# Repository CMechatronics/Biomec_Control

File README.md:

# Control. Biomec UMA

Biomec es una iniciativa de la Universidad de Málaga orientada al desarrollo de soluciones de ingeniería aplicadas a prótesis de mano electrónicas. El proyecto parte del estudio de señales electromiográficas (EMG), obtenidas a partir de la actividad muscular, para convertirlas en información útil de control.

La señal biológica se adquiere mediante un sistema de medida basado en el ADS1198 y se comunica con un microcontrolador encargado de procesarla. A partir de ese tratamiento es posible definir umbrales de activación y generar órdenes de control que permitan accionar los motores de la prótesis de forma coordinada.

El trabajo integra varias disciplinas técnicas, entre ellas mecánica, control, electrónica y diseño de sistemas embebidos.

## Objetivo del repositorio

Este repositorio reúne el trabajo del departamento de control y sirve como base para organizar el avance del proyecto, documentar decisiones técnicas y centralizar tareas, diseños y pruebas de desarrollo.

## Contexto técnico

El planteamiento del sistema se apoya en la adquisición diferencial de bioseñales, el acondicionamiento de la señal y su posterior interpretación para control. En la práctica, esto exige una interfaz fiable entre el cuerpo y la electrónica, así como un tratamiento adecuado del ruido, la amplitud de la señal y la sincronización con el sistema de actuación.

## Alcance

- Estudio y adquisición de señales EMG.
- Interfaz entre el sensor biológico y la electrónica de control.
- Procesamiento de señal para detección de umbrales y eventos.
- Integración con actuadores para el control de la mano protésica.

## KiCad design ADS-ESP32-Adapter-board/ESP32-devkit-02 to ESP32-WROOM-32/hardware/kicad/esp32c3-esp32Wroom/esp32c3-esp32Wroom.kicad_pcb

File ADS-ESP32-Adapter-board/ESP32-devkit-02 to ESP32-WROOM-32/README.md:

# Placa adaptadora: ESP32-DevKit-C3-02 → ESP32-WROOM-32

## Resumen ejecutivo

Este directorio contiene el diseño y documentación de la placa adaptadora que permite migrar del ESP32-C3 DevKitC-02 al ESP32-WROOM-32, manteniendo compatibilidad total con la interfaz del ADS1198 y reduciendo la dependencia de hardware específico.

## Motivación técnica

El ESP32-C3 DevKitC-02 presenta limitaciones de disponibilidad en el mercado y restricciones en número de pines GPIO. El ESP32-WROOM-32 ofrece:
- Mayor capacidad de procesamiento (2 núcleos vs 1)
- Más pines GPIO disponibles (34 vs 13)
- Mayor memoria RAM y flash
- Mejor disponibilidad en el mercado
- Mejor rendimiento energético en aplicaciones con WiFi/Bluetooth

La placa adaptadora permite cambiar de microcontrolador sin modificar la base del sistema ni el firmware de procesamiento de señal.

---

## Especificaciones técnicas comparativas

### Arquitectura y procesamiento

| Aspecto | ESP32-C3 DevKit-02 | ESP32-WROOM-32 |
|--------|-------------------|------------------|
| **Arquitectura** | RISC-V 32-bit | Xtensa 32-bit dual-core |
| **Núcleos** | 1 @ 160 MHz | 2 @ 80/160 MHz (configurable) |
| **Caché** | 16 KB I + 8 KB D | 32 KB I + 32 KB D (per core) |
| **Memoria RAM** | 400 KB | 520 KB |
| **Flash externo** | 4 MB | 4/8/16 MB (configurable) |
| **Voltaje** | 3.3 V | 3.3 V |
| **Consumo activo** | ~40-60 mA | ~80-100 mA (dual-core) |

### Conectividad

| Característica | ESP32-C3 | ESP32-WROOM-32 |
|---|---|---|
| **WiFi** | 802.11 b/g/n (2.4 GHz) | 802.11 b/g/n (2.4 GHz) |
| **Bluetooth** | LE 5.0 only | Classic 5.0 + LE 4.2 |
| **Antena** | Integrada PCB | Integrada PCB |
| **TX Power** | +15 dBm (WiFi), +4 dBm (BLE) | +20 dBm (WiFi), +4 dBm (BLE) |

### Periféricos disponibles

| Periférico | ESP32-C3 | ESP32-WROOM-32 |
|---|---|---|
| **UART** | 2 (GPIO20/21, GPIO5/6 alt) | 3 (GPIO1/3, GPIO9/10, GPIO17/16 alt) |
| **SPI** | 1 maestro (GPIO6/7/2/10) | 3 (SPI2 en GPIO12-15, SPI3 en GPIO17-22) |
| **I²C** | 2 | 2 (GPIO21/22) |
| **GPIO analógicos** | 11 canales ADC | 12 canales ADC (algunos compartidos con SPI) |
| **PWM** | 6 canales | 16 canales |
| **Timer** | 2 | 4 |
| **RTC** | Sí | Sí |

---

## Mapa de equivalencias GPIO

### Interfaz del ADS1198 (SPI principal)

| Función | ESP32-C3 DevKit-02 | ESP32-WROOM-32 | Notas |
|---------|-------------------|-----------------|-------|
| **FE_RESET** | GPIO0 | GPIO32 | Reinicio del front-end ADS1198 |
| **FE_DRDY** | GPIO1 | GPIO35 | Data Ready del ADS1198 |
| **SPI_MISO** | GPIO2 | GPIO12 | ESP32 ← ADS1198 (datos) |
| **FE_START** | GPIO3 | GPIO33 | Inicio de conversión del ADS |
| **SPI_CLK** | GPIO6 | GPIO14 | Reloj SPI |
| **SPI_MOSI** | GPIO7 | GPIO13 | ESP32 → ADS1198 (datos) |
| **FE_CS** | GPIO10 | GPIO15 | Chip Select del ADS1198 |

### Pines de soporte general

| Función | ESP32-C3 | ESP32-WROOM-32 | Observaciones |
|---------|----------|---|---|
| **3V3** | Pin 2 | Pin 2 | Alimentación lógica |
| **5V** | Pin 1 | Pin 1 | Entrada de alimentación externa |
| **GND** | Pins 3, 4, 5 | Pins 3, 4, 5 | Referencia común (múltiples puntos) |
| **USB D+** | GPIO19 | GPIO25 | No usado en este diseño |
| **USB D-** | GPIO18 | GPIO26 | No usado en este diseño |
| **EN/RST** | GPIO9 | GPIO EN | Reinicio del microcontrolador |
| **BOOT** | GPIO8 | GPIO0 alt | Modo de arranque |

### GPIO disponibles adicionales

Pines libres para futuras expansiones o depuración:

**ESP32-WROOM-32:**
- GPIO4, GPIO5, GPIO23, GPIO27, GPIO34, GPIO36, GPIO37, GPIO38, GPIO39
- GPIO25, GPIO26 (para USB si se requiere, no usado actualmente)

---

## Consideraciones de diseño

### Alimentación

- **Voltaje de entrada recomendado:** 5V ± 0.5V
- **Regulador:** LDO de bajo ruido para generar 3.3V
- **Capacitores:** 
  - Entrada: 10 µF (para estabilidad de línea de 5V)
  - Salida: 10 µF + 100 nF (cerca del ESP32-WROOM-32)
- **Consumo pico esperado:** ~150 mA (con WiFi activo)

### Aislamiento de ruido

El ADS1198 es un front-end de bajo ruido sensible a perturbaciones electromagnéticas:

- Separación física entre zona de alimentación del ADS1198 y ESP32-WROOM-32
- Plano de GND continuo bajo el ADS1198
- Vías de paso (via stitching) alrededor del área de señal analógica
- Capacitores de desacoplamiento locales (100 nF) para cada pin de alimentación del ADS

### Interfaces SPI

**ESP32-WROOM-32 SPI2 (usado):**
- Frecuencia configurada: 2 MHz (conservadora para estabilidad)
- Bus compartido con la interfaz SD (cuidado si se agrega soporte SD)
- Modo: SPI Master, CPOL=0, CPHA=0

**Líneas de control especiales:**
- **DRDY** es una línea de interrupción activa baja
- **CS** debe mantenerse baja durante toda la transacción SPI
- **RESET** debe pulsarse al menos 2 µs

### Protección ESD

- Protección ESD serie en líneas de señal analógica (optional, depende de ambiente)
- Protección TVS en líneas de GPIO si están expuestas

---

## Estructura del proyecto

```
ESP32-devkit-02 to ESP32-WROOM-32/
├── docs/
│   ├── planteamiento.pdf          # Análisis y justificación técnica
│   └── README.md                  # Este archivo
├── hardware/
│   └── kicad/
│       ├── esp32c3-esp32Wroom/   # Diseño principal de la placa
│       │   ├── esp32c3-esp32Wroom.kicad_sch
│       │   ├── esp32c3-esp32Wroom.kicad_pcb
│       │   ├── esp32c3-esp32Wroom.kicad_pro
│       │   └── .history/          # Historial de cambios
│       └── MiESP32Lib/            # Librería de símbolos personalizados
│           └── MiESP32Lib.kicad_sym
├── src/                           # Firmware en desarrollo
├── lib/                           # Librerías reutilizables
├── signal_processing/             # Módulos de procesamiento de señal
└── tools/                         # Scripts y utilidades
```

---

## Cambios de firmware necesarios

### Configuración de pines en PlatformIO/Arduino

```cpp
// Configuración SPI
#define SPI_MISO  12
#define SPI_MOSI  13
#define SPI_CLK   14
#define SPI_CS    15

// Señales de control del ADS1198
#define ADS_RESET 32
#define ADS_DRDY  35
#define ADS_START 33

// Verificar que el SPI esté configurado para SPI2:
// hspi_host en lugar de vspi_host
```

### Inicialización del SPI

```cpp
spi_bus_config_t buscfg = {
    .mosi_io_num = SPI_MOSI,
    .miso_io_num = SPI_MISO,
    .sclk_io_num = SPI_CLK,
    .quadwp_io_num = -1,
    .quadhd_io_num = -1,
    .max_transfer_sz = 4094,
};

esp_err_t ret = spi_bus_initialize(HSPI_HOST, &buscfg, DMA_CHAN_AUTO);
```

---

## Validación y pruebas

### Checklist de verificación hardware

- [ ] Continuidad en pistas de alimentación (5V, 3.3V, GND)
- [ ] Ausencia de cortocircuitos entre pistas de señal
- [ ] Voltaje de salida del regulador: 3.3V ± 0.1V
- [ ] Continuidad en líneas SPI (CLK, MOSI, MISO, CS)
- [ ] Continuidad en líneas de control (RESET, DRDY, START)
- [ ] Resistencia de Pull-up en DRDY (si está configurado)

### Pruebas funcionales

1. **Lectura de registro de identity del ADS1198**
   - Leer registro 0x00 (debe retornar ID del chip)
   - Repetir 10 veces para validar comunicación estable

2. **Adquisición de datos**
   - Configurar ADS1198 en modo continuo
   - Leer datos continuamente
   - Verificar rango esperado (±12V entrada → ±32768 digital)

3. **Rendimiento**
   - Medir frecuencia de muestreo efectiva (debe ser ≥ 1000 Hz)
   - Medir latencia de DRDY a lectura completa

4. **WiFi/Bluetooth** (si se requiere)
   - Verificar conectividad WiFi
   - Verificar rango de señal
   - Evaluar impacto en ruido de ADC

---

## Diferencias operacionales clave

### Ventajas del ESP32-WROOM-32

✅ **Dual-core:** Posibilidad de ejecutar procesamiento pesado en core 1 mientras core 0 gestiona SPI  
✅ **Más memoria:** Espacio para algoritmos de filtrado más complejos  
✅ **Mejor rendimiento WiFi:** Core dedicado disponible  
✅ **Mayor disponibilidad:** Componente más común en el mercado  
✅ **Menores costos:** Precio más estable y comprobado  

### Limitaciones a considerar

⚠️ **Consumo superior:** ~50 mA adicionales con dual-core activo  
⚠️ **Mayor tamaño:** PCB del módulo es más grande  
⚠️ **Configuración SPI:** Usa SPI2 en lugar de SPI1  
⚠️ **Pin layout diferente:** Requiere rediseño de placa adaptadora  
⚠️ **ADC compartido:** Algunos pines ADC comparten funciones con SPI (GPIO12, GPIO13, GPIO14, GPIO15)

---

## Hoja de ruta

| Fase | Tarea | Estado | Target |
|------|-------|--------|--------|
| 1 | Diseño esquemático y layout PCB | ✅ Completado | - |
| 2 | Fabricación de prototipo | ⏳ En progreso | 2-3 semanas |
| 3 | Validación eléctrica del prototipo | ⏳ En progreso | - |
| 4 | Adaptación de firmware a pines nuevos | ⏳ En progreso | - |
| 5 | Pruebas funcionales del sistema completo | ⏹️ Pendiente | - |
| 6 | Generación de PCB final | ⏹️ Pendiente | - |
| 7 | Documentación de fabricación | ⏹️ Pendiente | - |

---

## Referencias y recursos

### Datasheets
- [ESP32-C3 Datasheet](https://www.espressif.com/sites/default/files/documentation/esp32-c3_datasheet_en.pdf)
- [ESP32 (WROOM-32) Datasheet](https://www.espressif.com/sites/default/files/documentation/esp32_datasheet_en.pdf)
- [ADS1198 Datasheet](https://www.ti.com/lit/ds/symlink/ads1198.pdf)

### Librerías y soporte
- [ESP-IDF (Espressif IoT Development Framework)](https://github.com/espressif/esp-idf)
- [Arduino-ESP32](https://github.com/espressif/arduino-esp32)
- [KiCad Documentation](https://docs.kicad.org/)

### Herramientas recomendadas
- KiCad 6.0+ para editar esquemáticos y PCB
- PlatformIO o Arduino IDE para programación
- Logic Analyzer de bajo coste para debug SPI

---

## Contacto y soporte

Para consultas técnicas sobre este diseño, consultar la documentación de Biomec UMA o la rama `develop` del repositorio.

**Última actualización:** Agosto 2026  
**Autor:** Departamento de Control, Biomec UMA  
**Licencia:** Ver archivo LICENSE en la raíz del repositorio

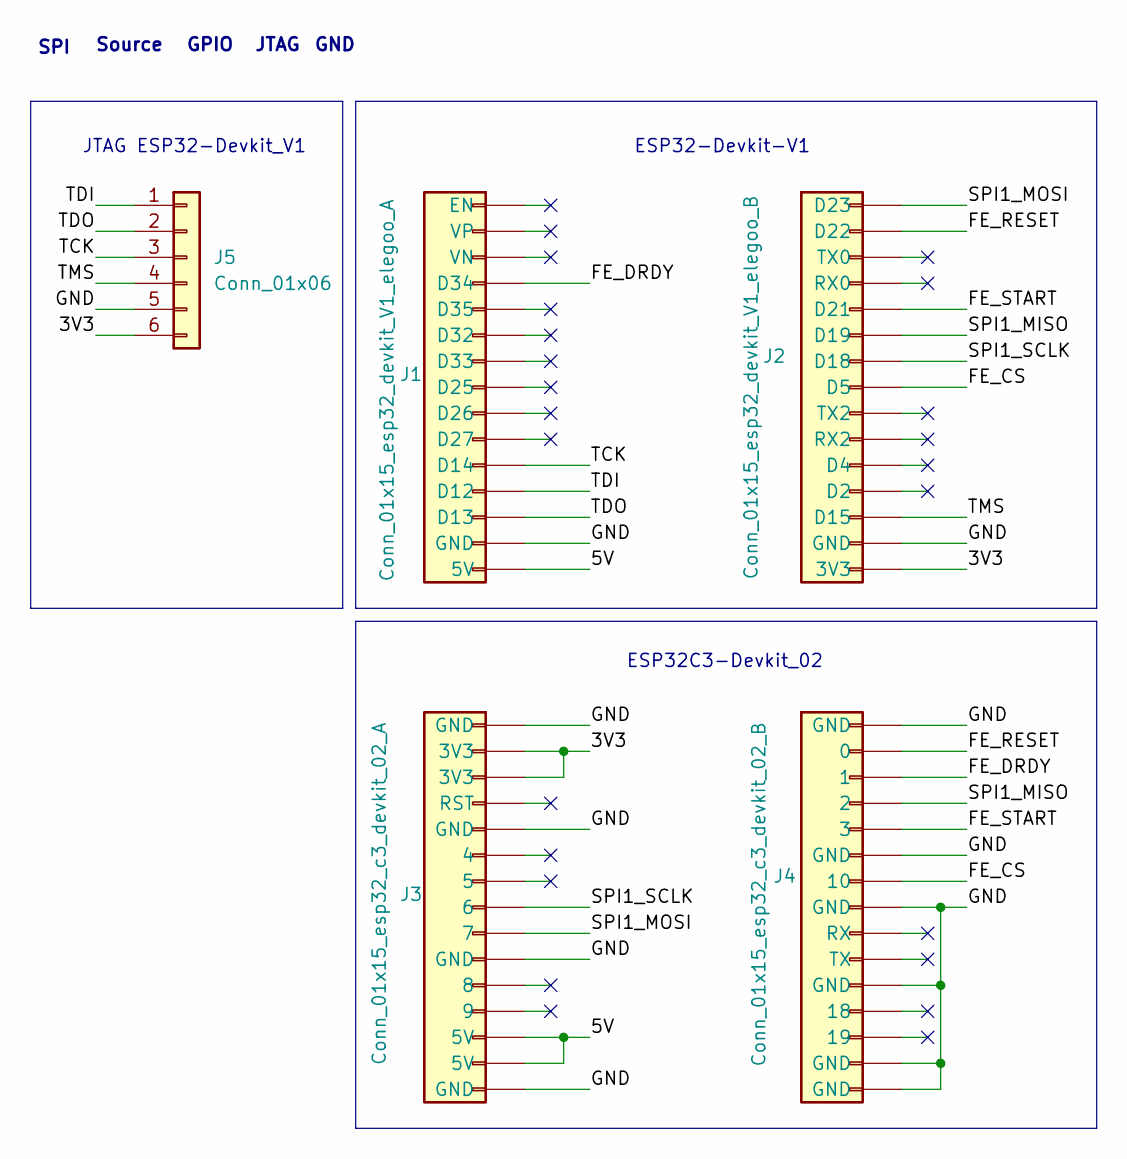
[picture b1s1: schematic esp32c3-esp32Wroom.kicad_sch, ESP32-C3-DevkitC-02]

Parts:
J1: Conn_01x15_esp32_devkit_V1_elegoo_A; PinSocket_1x15_P2.54mm_Vertical
J2: Conn_01x15_esp32_devkit_V1_elegoo_B; PinSocket_1x15_P2.54mm_Vertical
J3: Conn_01x15_esp32_c3_devkit_02_A; PinHeader_1x15_P2.54mm_Vertical
J4: Conn_01x15_esp32_c3_devkit_02_B; PinHeader_1x15_P2.54mm_Vertical
J5: Conn_01x06; PinSocket_1x06_P2.54mm_Vertical

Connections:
/3V3: J2.15 (3V3), J3.2 (3V3), J3.3 (3V3), J5.6
/5V: J1.15 (5V), J3.13 (5V), J3.14 (5V)
/FE_CS: J2.8 (D5), J4.7 (10)
/FE_DRDY: J1.4 (D34), J4.3 (1)
/FE_RESET: J2.2 (D22), J4.2 (0)
/FE_START: J2.5 (D21), J4.5 (3)
/GND: J1.14 (GND), J2.14 (GND), J3.1 (GND), J3.5 (GND), J3.10 (GND), J3.15 (GND), J4.1 (GND), J4.6 (GND), J4.8 (GND), J4.11 (GND), J4.14 (GND), J4.15 (GND), J5.5
/SPI1_MISO: J2.6 (D19), J4.4 (2)
/SPI1_MOSI: J2.1 (D23), J3.9 (7)
/SPI1_SCLK: J2.7 (D18), J3.8 (6)
/TCK: J1.11 (D14), J5.3
/TDI: J1.12 (D12), J5.1
/TDO: J1.13 (D13), J5.2
/TMS: J2.13 (D15), J5.4

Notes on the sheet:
ESP32C3-Devkit_02
JTAG
GND
GPIO
Source
ESP32-Devkit-V1
JTAG ESP32-Devkit_V1
SPI

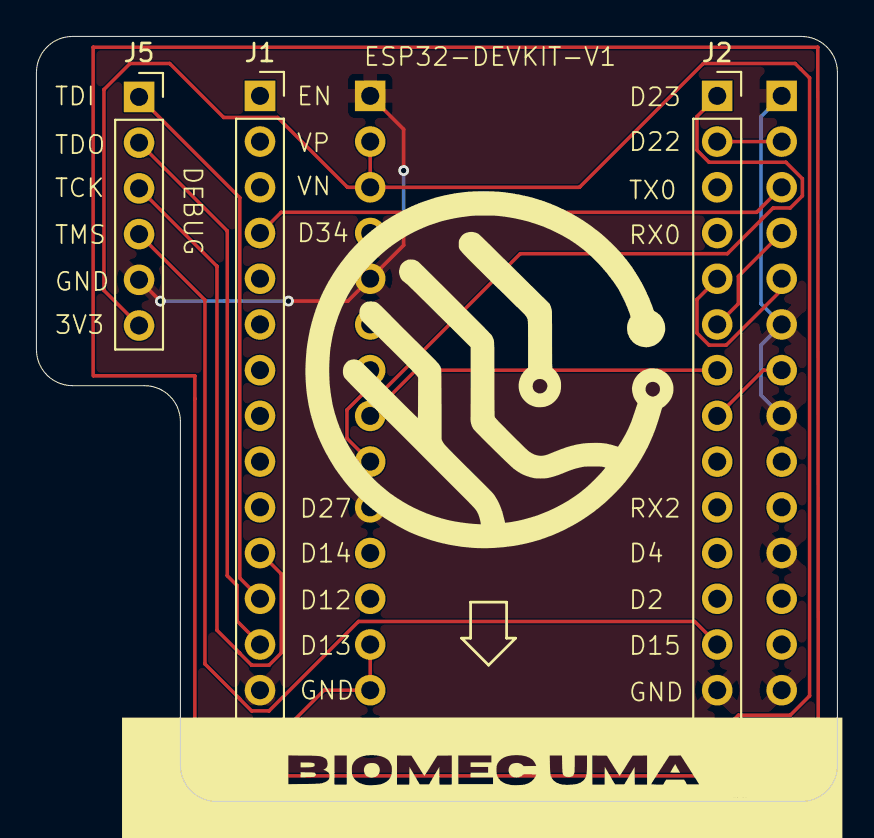
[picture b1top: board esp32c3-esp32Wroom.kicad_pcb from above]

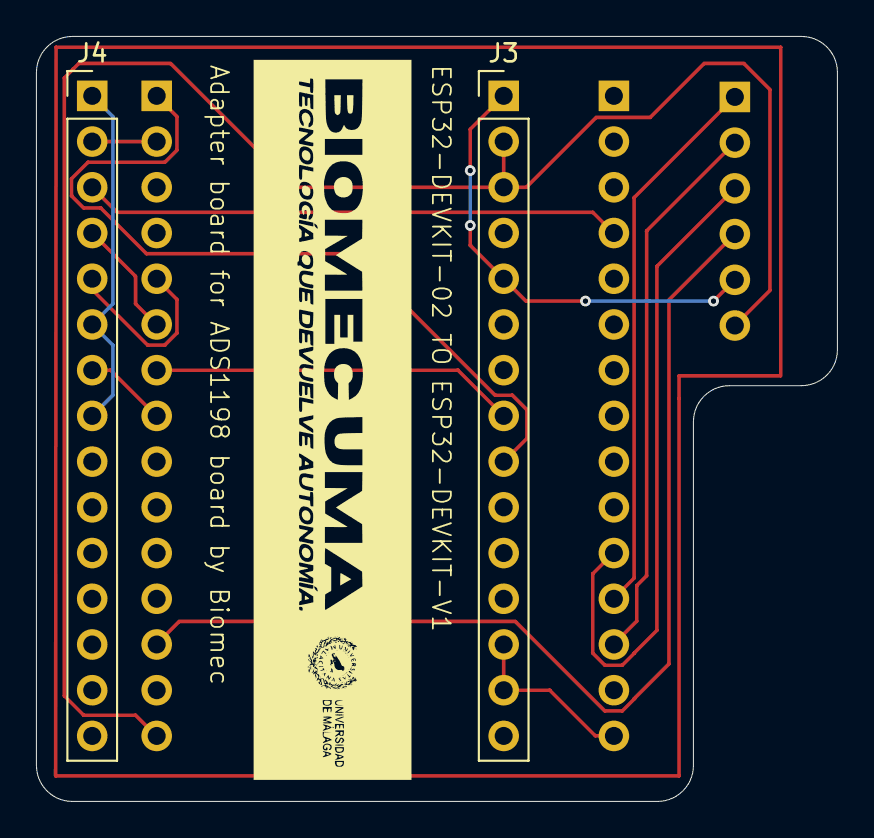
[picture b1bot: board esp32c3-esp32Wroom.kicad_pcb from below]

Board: 2 copper layers, 44.5 x 42.5 mm, 5 parts (2 on the bottom side), 14 nets.
